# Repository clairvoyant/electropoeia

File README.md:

# electropoeia
Ruminations on hardware and software product development

Contents
--------

This repository contains experiments related to electronics. 
The experiments are carried to understand and evaluate the effort of more complex electronics products. 

Any experiment evaluating hardware can be added to the subdirectories including but not limited to:
   * TI MPS430 based project
   * AVR based projects
   * ESP12 based projects
   * Hybrid circuits. 

The methodology used in the development of the projects carry three steps. 
   * Rapid prototyping. 
     This phase reuses as much resources from off-the-shelf components at possible. 
     The objetive is to create rapid iterations to mature the project. 
     STL and 3D models of the product are not expected in this phase. 
      * Tools: Spice, Arduino, Rasperry Pi, Parallel port GPIO, electronic kits. 
      * Inputs: Design files
      * Outputs: Code,  electronics skeches. spice simulation. 
      * Metrics: Time employed in the definition and development. 

  * Product mature. 
     This phase is used to evalute the cost of the model. 
     The objetive is to create an usable product. 
     STL and 3D models of the product are expected in this phase. 
      * Tools: Spice, Kicad, LibreCad, FreeCad, 
      * Inputs: Code and skeches from previous phase.
      * Outputs: Schematics, PCB, Gerber, 3D model, assembly, product photography, viability and cost assesment document.  Postmorten document.

  * Product consolidation. 
      This phase is used to create a product that can be mass produced product.
     The objetive is to create a product that can be sell in a competitive market and survive. 
     Special focus on items like propagation, security and usage shall be taken into account. 
      * Tools: Spice, Kicad, LibreCad, FreeCad, 
      * Inputs: Files from previous phase. 
      * Outputs: Schematics, PCB, Gerber, 3D model, assembly, final product photography, viability and cost assesment document.

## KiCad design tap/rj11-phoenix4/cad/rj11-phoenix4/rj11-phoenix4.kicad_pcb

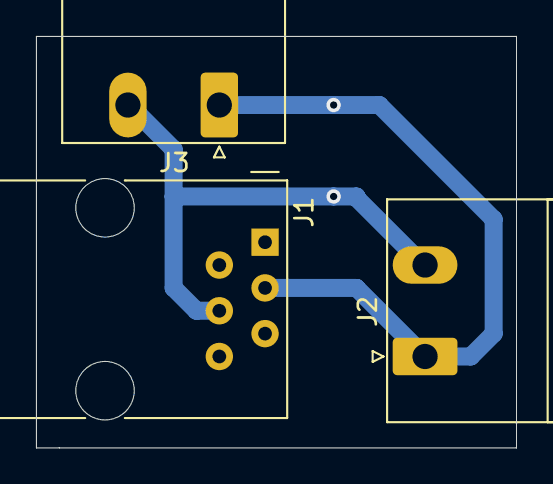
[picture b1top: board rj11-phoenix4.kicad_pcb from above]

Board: 2 copper layers, 26.7 x 22.9 mm, 3 parts (0 on the bottom side), 2 nets.

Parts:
J1: RJ12; RJ12_Amphenol_54601
J2, J3: Screw_Terminal_01x02; PhoenixContact_MSTBA_2,5_2-G-5,08_1x02_P5.08mm_Horizontal

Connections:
unnamed: J1.3, J2.1, J3.1
unnamed: J1.4, J2.2, J3.2

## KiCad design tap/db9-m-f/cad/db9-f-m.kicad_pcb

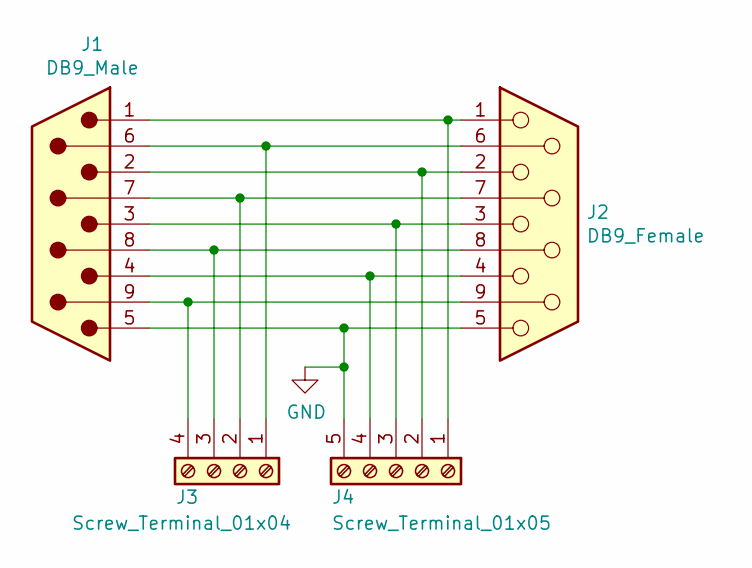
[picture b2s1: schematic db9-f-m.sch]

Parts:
J1: DB9_Male; DSUB-9_Male_Horizontal_P2.77x2.84mm_EdgePinOffset9.40mm
J2: DB9_Female; DSUB-9_Female_Horizontal_P2.77x2.84mm_EdgePinOffset9.40mm
J3: Screw_Terminal_01x04; PhoenixContact_MC_1,5_4-G-3.5_1x04_P3.50mm_Horizontal
J4: Screw_Terminal_01x05; PhoenixContact_MC_1,5_5-G-3.5_1x05_P3.50mm_Horizontal

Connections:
GND: J1.5, J2.5, J4.5
unnamed: J1.1, J2.1, J4.1
unnamed: J1.2, J2.2, J4.2
unnamed: J1.3, J2.3, J4.3
unnamed: J1.4, J2.4, J4.4
unnamed: J1.6, J2.6, J3.1
unnamed: J1.7, J2.7, J3.2
unnamed: J1.8, J2.8, J3.3
unnamed: J1.9, J2.9, J3.4

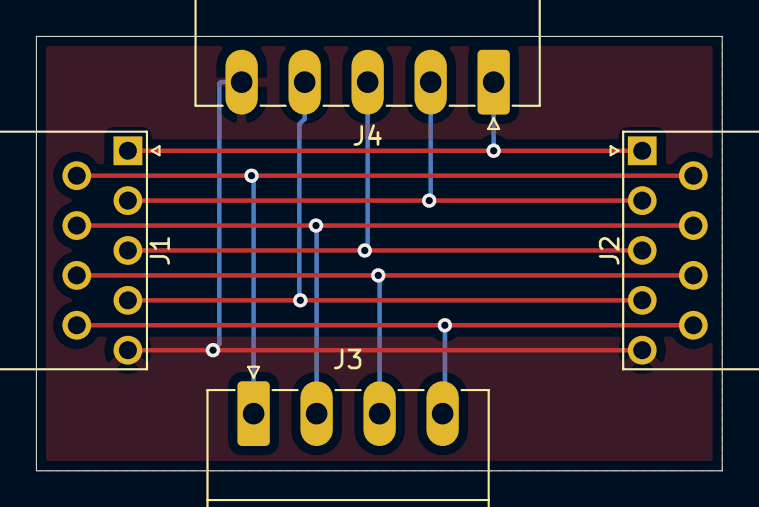
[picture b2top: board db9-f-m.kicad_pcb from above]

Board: 2 copper layers, 38.1 x 24.1 mm, 4 parts (0 on the bottom side), 9 nets.

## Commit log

2018-01-04 NEW: first commit
2018-01-04 basic working.
    * ino files compile
    * fritzing draw and checked visualy.
2018-01-04 README update to point out the vector7 compile error.
2018-01-05 NEW: used tools.
2018-01-10 FIX: relaxed annoying tone
2020-07-16 tap added
2021-03-04 Added RJ12 tap.
